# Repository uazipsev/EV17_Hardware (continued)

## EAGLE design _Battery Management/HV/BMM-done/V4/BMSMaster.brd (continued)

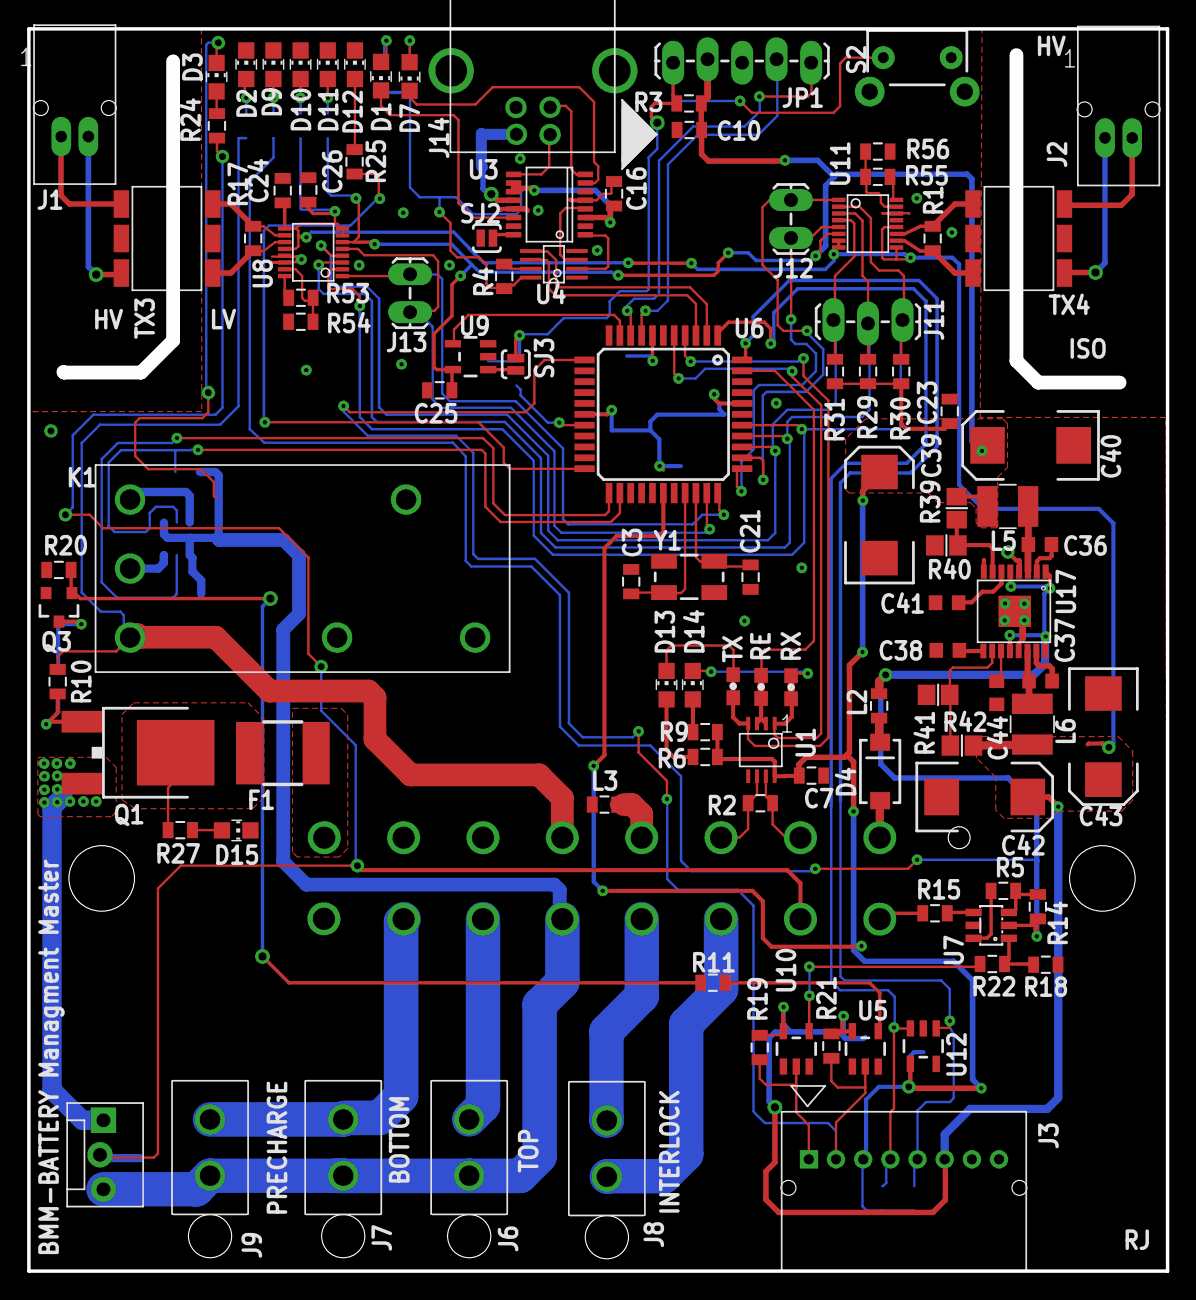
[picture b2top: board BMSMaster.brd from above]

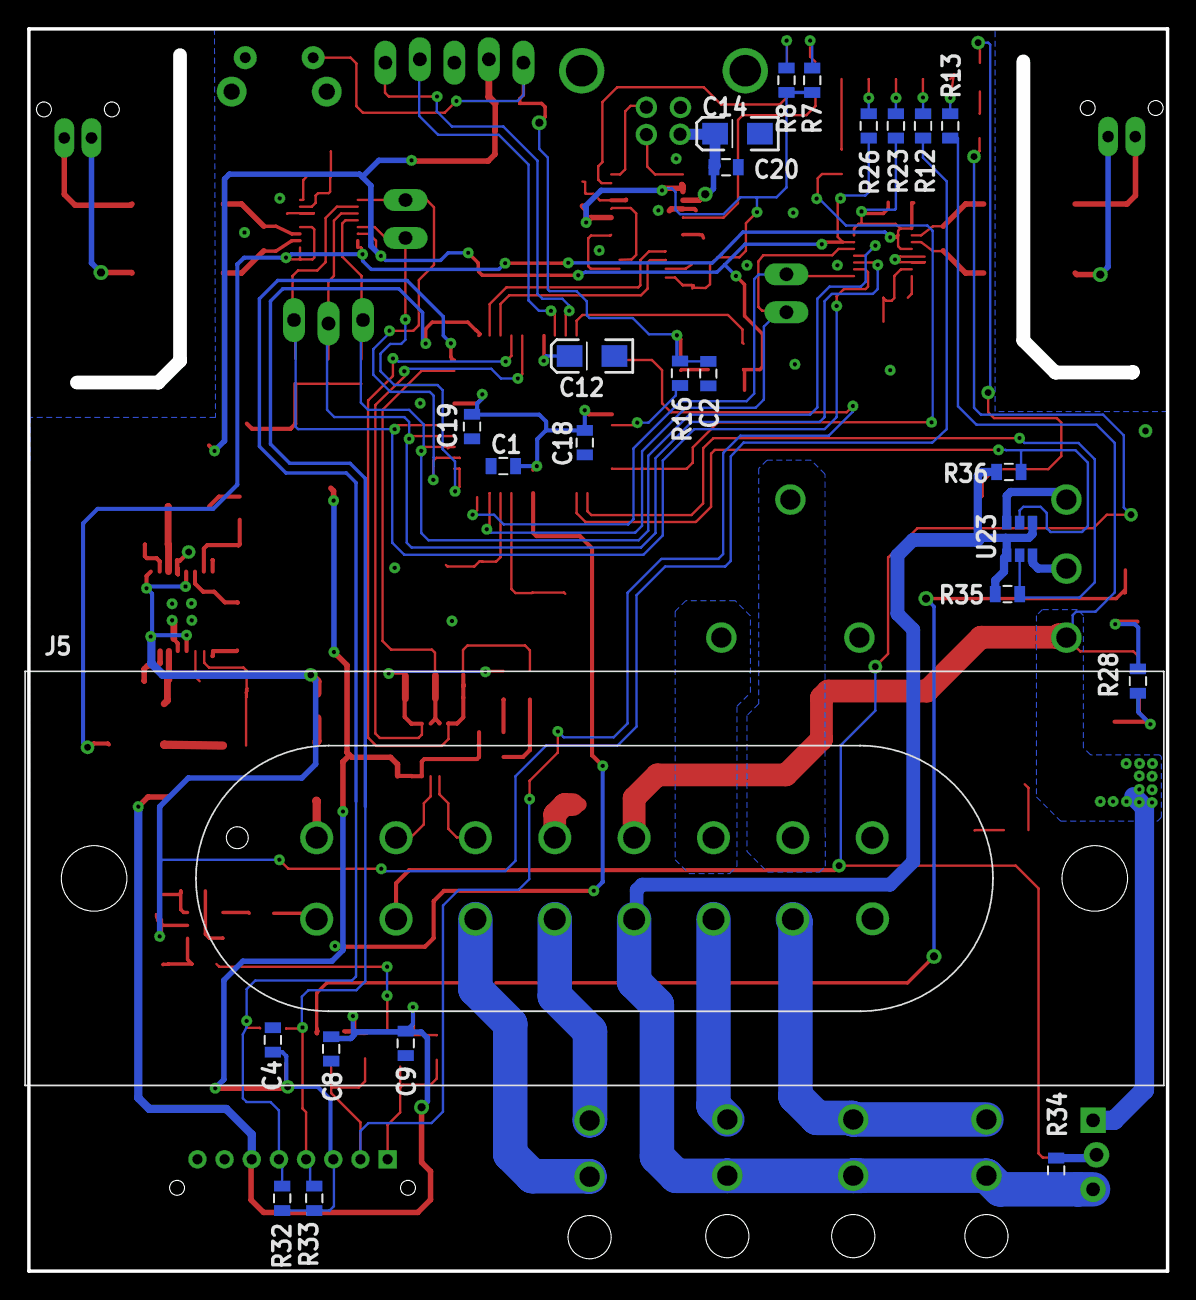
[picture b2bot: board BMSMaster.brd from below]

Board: 2 copper layers, 83.8 x 91.4 mm, 129 parts (25 on the bottom side), 100 nets.

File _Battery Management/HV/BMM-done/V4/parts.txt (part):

Partlist

Exported from BMSMaster.sch at 4/28/2016 8:13 PM

EAGLE Version 7.5.0 Copyright (c) 1988-2015 CadSoft

Assembly variant: 

Part     Value             Device                  Package                  Library                    Sheet

C1       0.1UF             CAP_0.1UF_50V_0805      0805                     FSAE Electric              1
C2       0.1UF             CAP_0.1UF_50V_0805      0805                     FSAE Electric              1
C3       12PF              CAP_12PF_50V_0805       0805                     FSAE Electric              1
C4       0.1UF             CAP_0.1UF_50V_0805      0805                     FSAE Electric              1
C5       10UF              CAP-POL_10UF_16V        EIA3216-16V              FSAE Electric              1
C6       10UF              CAP-POL_10UF_16V        EIA3216-16V              FSAE Electric              1
C7       0.1UF             CAP_0.1UF_50V_0805      0805                     FSAE Electric              1
C8       0.1UF             CAP_0.1UF_50V_0805      0805                     FSAE Electric              1
C9       0.1UF             CAP_0.1UF_50V_0805      0805                     FSAE Electric              1
C12      10UF              CAP-POL_10UF_16V        EIA3216-16V              FSAE Electric              1
C14      10UF              CAP-POL_10UF_16V        EIA3216-16V              FSAE Electric              1
C16      0.1UF             CAP_0.1UF_50V_0805      0805                     FSAE Electric              1
C18      0.1UF             CAP_0.1UF_50V_0805      0805                     FSAE Electric              1
C19      0.1UF             CAP_0.1UF_50V_0805      0805                     FSAE Electric              1
C20      0.1UF             CAP_0.1UF_50V_0805      0805                     FSAE Electric              1
C21      12PF              CAP_12PF_50V_0805       0805                     FSAE Electric              1
C23      0.1UF             CAP_0.1UF_50V_0805      0805                     FSAE Electric              1
C24      0.1UF             CAP_0.1UF_50V_0805      0805                     FSAE Electric              1
C25      0.1UF             CAP_0.1UF_50V_0805      0805                     FSAE Electric              1
C26      0.1UF             CAP_0.1UF_50V_0805      0805                     FSAE Electric              1
C27      10UF              CAP-POL_10UF_16V        EIA3216-16V              FSAE Electric              1
C28      10UF              CAP-POL_10UF_16V        EIA3216-16V              FSAE Electric              1
D1       GREEN             LED_GREEN               CHIP_LED0805             FSAE Electric              1
D2       GREEN             LED_GREEN               CHIP_LED0805             FSAE Electric              1
D3       ORANGE            LED_ORANGE              CHIP_LED0805             FSAE Electric              1
D4       RF201L2STE25      DIODE_RF201L2STE25      SMA                      FSAE Electric              1
D7       GREEN             LED_GREEN               CHIP_LED0805             FSAE Electric              1
D9       GREEN             LED_GREEN               CHIP_LED0805             FSAE Electric              1
D10      GREEN             LED_GREEN               CHIP_LED0805             FSAE Electric              1
D11      GREEN             LED_GREEN               CHIP_LED0805             FSAE Electric              1
D12      AMBER             LED_AMBER               CHIP_LED0805             FSAE Electric              1
D13      GREEN             LED_GREEN               CHIP_LED0805             FSAE Electric              1
D14      RED               LED_RED                 CHIP_LED0805             FSAE Electric              1
D15      GREEN             LED_GREEN               CHIP_LED0805             FSAE Electric              1
f       550MA             PTC_550MA_60V           2018                     FSAE Electric              1
J1       M2_DF13-2P        M2_DF13-2P              DF13-2P                  FSAE Electric              1
J2       M2_DF13-2P        M2_DF13-2P              DF13-2P                  FSAE Electric              1
J3       M4_1X4_LOCK       M4_1X4_LOCK             MOLEX_1X4                FSAE Electric              1
J4       M80022232081-2    M80022232081-2          MOLEX-1X8-2              FSAE Electric              1
J5       M16_M_194280016   M16_M_194280016         19428-0016               FSAE Electric              1
J6       M2770166          M2770166                1-770166-0               FSAE Electric              1
J7       M2770166          M2770166                1-770166-0               FSAE Electric              1
J8       M2770166          M2770166                1-770166-0               FSAE Electric              1
J9       M2770166          M2770166                1-770166-0               FSAE Electric              1
J10      IMD               M3M1X3                  MOLEX-1X3                FSAE Electric              1
JP1                        M05LOCK_LONGPADS        1X05_LOCK_LONGPADS       SparkFun-Connectors        1
K1       ADJ14024          ADJ14024                ADJ14024                 FSAE Electric              1
L2       L_FB_2A           L_FB_2A                 0805                     FSAE Electric              1
L3       L_FB_2A           L_FB_2A                 0805                     FSAE Electric              1
L5       L_FB_2A           L_FB_2A                 0805                     FSAE Electric              1
Q1       IRFR9120TRPBF     MOS-P_IRFR9120TRPBF     DPAK                     FSAE Electric              1
Q3       BSS123            MOS-N_BSS123            SOT23                    FSAE Electric              1
R1       120               RES_120_1%_0805         0805                     FSAE Electric              1
R2       120               RES_120_1%_0805         0805                     FSAE Electric              1
R3       10K               RES_10K_1%_0805         0805                     FSAE Electric              1
R4       1K                RES_1K_1%_0805          0805                     FSAE Electric              1
R5       1K                RES_1K_1%_0805          0805                     FSAE Electric              1
R6       1k                RES_1K_1%_0805          0805                     FSAE Electric              1
R7       1K                RES_1K_1%_0805          0805                     FSAE Electric              1
R8       1K                RES_1K_1%_0805          0805                     FSAE Electric              1
R9       1k                RES_1K_1%_0805          0805                     FSAE Electric              1
R10      22K               RES_22K_1%_0805         0805                     FSAE Electric              1
R11      1K                RES_1K_1%_0805          0805                     FSAE Electric              1
R12      1.2K              RES_1.2K_1%_0805        0805                     FSAE Electric              1
R13      3.3K              RES_3.3K_1%_0805        0805                     FSAE Electric              1
R14      10K               RES_10K_1%_0805         0805                     FSAE Electric              1
R15      10K               RES_10K_1%_0805         0805                     FSAE Electric              1
R16      499               RES_499_1%_0805         0805                     FSAE Electric              1
R17      120               RES_120_1%_0805         0805                     FSAE Electric              1
R18      100K              RES_100K_1%_0805        0805                     FSAE Electric              1
R19      2.2K              RES_2.2K_1%_0805        0805                     FSAE Electric              1
R20      100K              RES_100K_1%_0805        0805                     FSAE Electric              1
R21      2.2K              RES_2.2K_1%_0805        0805                     FSAE Electric              1
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
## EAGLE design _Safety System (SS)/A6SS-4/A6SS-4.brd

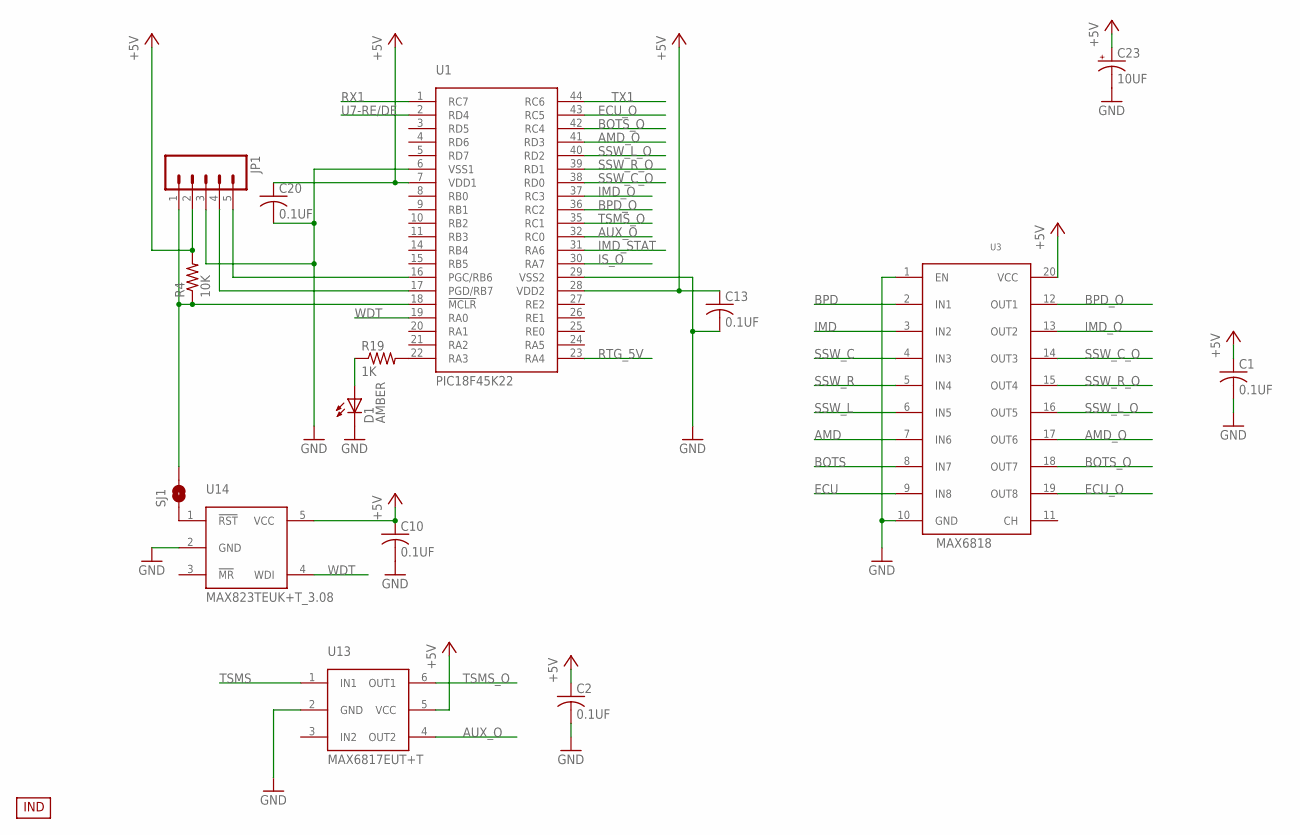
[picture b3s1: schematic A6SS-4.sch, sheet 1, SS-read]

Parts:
C1, C2, C10, C13, C20: 0.1UF; 0805
C23: 10UF; EIA3216-16V
D1: AMBER; CHIP_LED0805
JP1: M05LOCK_LONGPADS; 1X05_LOCK_LONGPADS
R4: 10K; 0805
R19: 1K; 0805
SJ1: SOLDERJUMPERNO; SJ_2S-NO
U1: PIC18F45K22; TQFP-44
U3: MAX6818; SSOP-20
U13: MAX6817EUT+T; SOT23-6
U14: MAX823TEUK+T_3.08; SOT23-5
U$1: INDPK1; PICKIT-PIN-1

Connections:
+5V: C1.1 (+), C2.1 (+), C10.1 (+), C13.1 (+), C20.1 (+), C23.A (+), JP1.2, R4.2, U1.7 (VDD1), U1.28 (VDD2), U3.20 (VCC), U13.5 (VCC), U14.5 (VCC); also elsewhere on the board
AMD: U3.7 (IN6); also elsewhere on the board
AMD_O: U1.41 (RD3), U3.17 (OUT6)
AUX_O: U1.32 (RC0), U13.4 (OUT2)
BOTS: U3.8 (IN7); also elsewhere on the board
BOTS_O: U1.42 (RC4), U3.18 (OUT7)
BPD: U3.2 (IN1); also elsewhere on the board
BPD_O: U1.36 (RC2), U3.12 (OUT1)
ECU: U3.9 (IN8); also elsewhere on the board
ECU_O: U1.43 (RC5), U3.19 (OUT8)
GND: C1.2 (-), C2.2 (-), C10.2 (-), C13.2 (-), C20.2 (-), C23.C (-), D1.C, JP1.3, U1.6 (VSS1), U1.29 (VSS2), U3.1 (EN), U3.10 (GND), U13.2 (GND), U14.2 (GND); also elsewhere on the board
IMD: U3.3 (IN2); also elsewhere on the board
IMD_O: U1.37 (RC3), U3.13 (OUT2)
IMD_STAT: U1.31 (RA6); also elsewhere on the board
IS_O: U1.30 (RA7); also elsewhere on the board
unnamed: SJ1.1, U14.1 (!RST)
unnamed: D1.A, R19.1
unnamed: R19.2, U1.22 (RA3)
unnamed: JP1.4, U1.17 (PGD/RB7)
unnamed: JP1.5, U1.16 (PGC/RB6)
unnamed: JP1.1, R4.1, SJ1.2, U1.18 (!MCLR)
RTG_5V: U1.23 (RA4); also elsewhere on the board
RX1: U1.1 (RC7); also elsewhere on the board
SSW_C: U3.4 (IN3); also elsewhere on the board
SSW_C_O: U1.38 (RD0), U3.14 (OUT3)
SSW_L: U3.6 (IN5); also elsewhere on the board
SSW_L_O: U1.40 (RD2), U3.16 (OUT5)
SSW_R: U3.5 (IN4); also elsewhere on the board
SSW_R_O: U1.39 (RD1), U3.15 (OUT4)
TSMS: U13.1 (IN1); also elsewhere on the board
TSMS_O: U1.35 (RC1), U13.6 (OUT1)
TX1: U1.44 (RC6); also elsewhere on the board
U7-RE/DE: U1.2 (RD4); also elsewhere on the board
WDT: U1.19 (RA0), U14.4 (WDI)

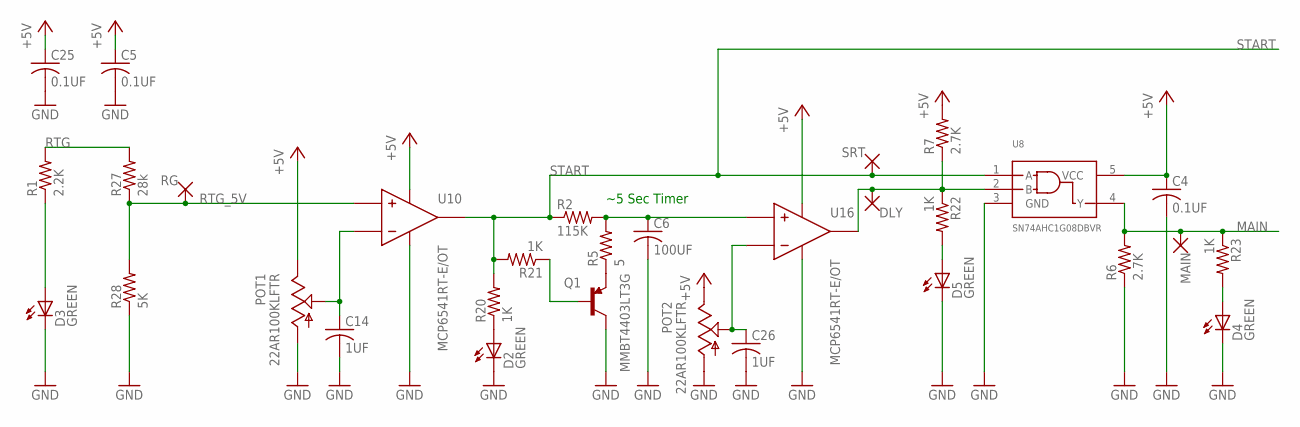
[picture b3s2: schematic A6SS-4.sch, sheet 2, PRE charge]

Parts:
C4, C5, C25: 0.1UF; 0805
C6: 100UF; 1206
C14, C26: 1UF; 0805
D2, D3, D4, D5: GREEN; CHIP_LED0805
DLY: TP; 0603
MAIN: TP; 0603
POT1, POT2: 22AR100KLFTR
Q1: MMBT4403LT3G; SOT23
R1: 2.2K; 0805
R2: 115K; 0805
R5: 5; 0805
R6, R7: 2.7K; 0805
R20, R21, R22, R23: 1K; 0805
R27: 28k; 0805
R28: 5K; 0805
RG: TP; 0603
SRT: TP; 0603
U8: SN74AHC1G08DBVR; SOT23-5
U10, U16: MCP6541RT-E/OT; SOT23-5

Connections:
+5V: C4.1 (+), C5.1 (+), C25.1 (+), POT1.1 (CCW), POT2.1 (CCW), R7.2, U8.5 (VCC), U10.2 (VDD), U16.2 (VDD); also elsewhere on the board
GND: C4.2 (-), C5.2 (-), C6.2 (-), C14.2 (-), C25.2 (-), C26.2 (-), D2.C, D3.C, D4.C, D5.C, POT1.3 (CW), POT2.3 (CW), Q1.3 (C), R6.1, R28.1, U8.3 (GND), U10.5 (GND), U16.5 (GND); also elsewhere on the board
MAIN: MAIN.1, MAIN.2, R6.2, R23.1, U8.4 (Y); also elsewhere on the board
unnamed: C26.1 (+), POT2.2 (W), U16.4 (-)
unnamed: Q1.1 (B), R21.1
unnamed: Q1.2 (E), R5.1
unnamed: C14.1 (+), POT1.2 (W), U10.4 (-)
unnamed: D2.A, R20.1
unnamed: D3.A, R1.1
unnamed: C6.1 (+), R2.2, R5.2, U16.3 (+)
unnamed: DLY.1, DLY.2, R7.1, R22.1, U8.2 (B), U16.1 (VOUT)
unnamed: D4.A, R23.2
unnamed: D5.A, R22.2
RTG: R1.2, R27.2; also elsewhere on the board
RTG_5V: R27.1, R28.2, RG.1, RG.2, U10.3 (+); also elsewhere on the board
START: R2.1, R20.2, R21.2, SRT.1, SRT.2, U8.1 (A), U10.1 (VOUT); also elsewhere on the board

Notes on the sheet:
~5 Sec Timer

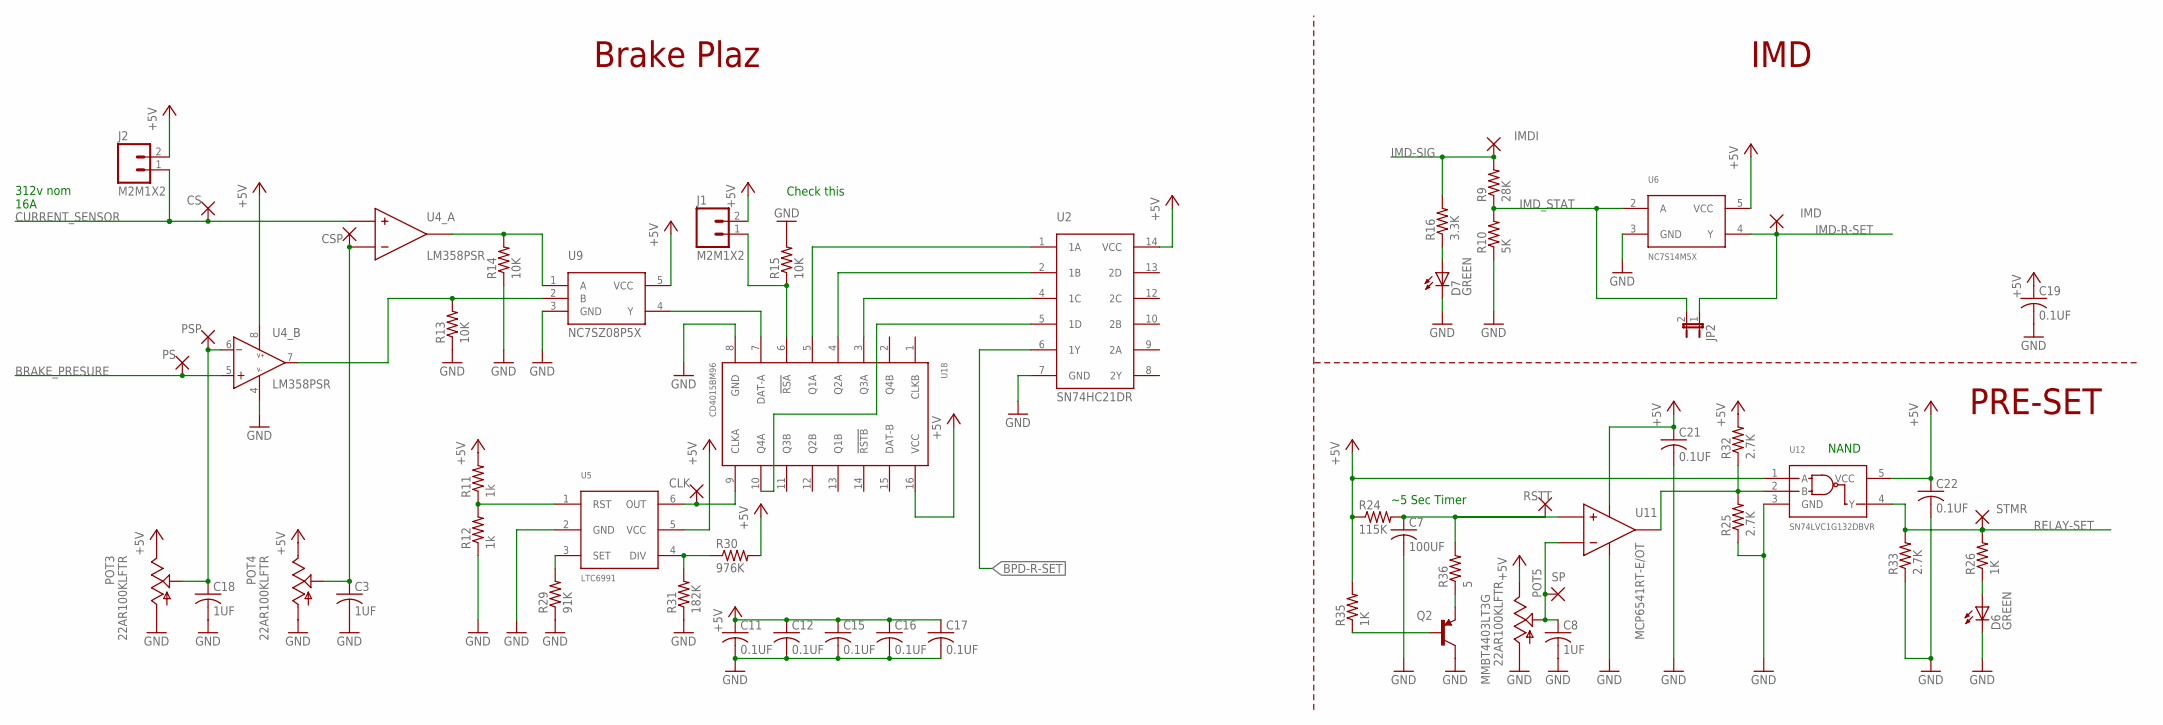
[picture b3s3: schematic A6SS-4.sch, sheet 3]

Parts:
C3, C8, C18: 1UF; 0805
C7: 100UF; 1206
C11, C12, C15, C16, C17, C19, C21, C22: 0.1UF; 0805
CLK: TP; 0603
CS: TP; 0603
CSP: TP; 0603
D6, D7: GREEN; CHIP_LED0805
IMD: TP; 0603
IMDI: TP; 0603
J1, J2: M2M1X2; MOLEX-1X2
JP2: JUMPER-2SMD-NO; SJ_2S-NO
POT3, POT4, POT5: 22AR100KLFTR
PS: TP; 0603
PSP: TP; 0603
Q2: MMBT4403LT3G; SOT23
R9: 28K; 0805
R10: 5K; 0805
R11, R12: 1k; 0805
R13, R14, R15: 10K; 0805
R16: 3.3K; 0805
R24: 115K; 0805
R25, R32, R33: 2.7K; 0805
R26, R35: 1K; 0805
R29: 91K; 0805
R30: 976K; 0805
R31: 182K; 0805
R36: 5; 0805
RSTT: TP; 0603
SP: TP; 0603
STMR: TP; 0603
U2: SN74HC21DR; SO-14
U4: LM358PSR; SO-8
U5: LTC6991; TSOT-23-6
U6: NC7S14M5X; SOT23-5
U9: NC7SZ08P5X; SC-70-5
U11: MCP6541RT-E/OT; SOT23-5
U12: SN74LVC1G132DBVR; SOT23-5
U18: CD4015BM96; SO-16

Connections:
+5V: C11.1 (+), C12.1 (+), C15.1 (+), C16.1 (+), C17.1 (+), C19.1 (+), C21.1 (+), C22.1 (+), J1.2, J2.2, POT3.1 (CCW), POT4.1 (CCW), POT5.1 (CCW), R11.2, R24.1, R30.2, R32.2, R35.2, U2.14 (VCC), U4.8 (V+), U5.5 (VCC), U6.5 (VCC), U9.5 (VCC), U11.2 (VDD), U12.1 (A), U12.5 (VCC), U18.16 (VCC); also elsewhere on the board
BPD-R-SET: U2.6 (1Y); also elsewhere on the board
BRAKE_PRESURE: PS.1, PS.2, U4.5 (+); also elsewhere on the board
CURRENT_SENSOR: CS.1, CS.2, J2.1, U4.3 (+); also elsewhere on the board
GND: C3.2 (-), C7.2 (-), C8.2 (-), C11.2 (-), C12.2 (-), C15.2 (-), C16.2 (-), C17.2 (-), C18.2 (-), C19.2 (-), C21.2 (-), C22.2 (-), D6.C, D7.C, POT3.3 (CW), POT4.3 (CW), POT5.3 (CW), Q2.3 (C), R10.1, R12.1, R13.1, R14.1, R15.2, R25.1, R29.1, R31.1, R33.1, U2.7 (GND), U4.4 (V-), U5.2 (GND), U6.3 (GND), U9.3 (GND), U11.5 (GND), U12.3 (GND), U18.8 (GND); also elsewhere on the board
IMD-R-SET: IMD.1, IMD.2, JP2.1, U6.4 (Y); also elsewhere on the board
IMD-SIG: IMDI.1, IMDI.2, R9.2, R16.2; also elsewhere on the board
IMD_STAT: JP2.2, R9.1, R10.2, U6.2 (A); also elsewhere on the board
unnamed: C8.1 (+), POT5.2 (W), SP.1, SP.2, U11.4 (-)
unnamed: U2.5 (1D), U18.10 (Q4A)
unnamed: R30.1, R31.2, U5.4 (DIV)
unnamed: D7.A, R16.1
unnamed: U9.4 (Y), U18.7 (DAT-A)
unnamed: J1.1, R15.1, U18.6 (!RSA)
unnamed: U2.1 (1A), U18.5 (Q1A)
unnamed: U2.2 (1B), U18.4 (Q2A)
unnamed: U2.4 (1C), U18.3 (Q3A)
unnamed: R29.2, U5.3 (SET)
unnamed: CLK.1, CLK.2, U5.6 (OUT), U18.9 (CLKA)
unnamed: C3.1 (+), CSP.1, CSP.2, POT4.2 (W), U4.2 (-)
unnamed: R25.2, R32.1, U11.1 (VOUT), U12.2 (B)
unnamed: R11.1, R12.2, U5.1 (RST)
unnamed: C18.1 (+), POT3.2 (W), PSP.1, PSP.2, U4.6 (-)
unnamed: R14.2, U4.1 (VOUT), U9.1 (A)
unnamed: D6.A, R26.1
unnamed: R13.2, U4.7 (O), U9.2 (B)
unnamed: Q2.1 (B), R35.1
unnamed: Q2.2 (E), R36.1
unnamed: C7.1 (+), R24.2, R36.2, RSTT.1, RSTT.2, U11.3 (+)
RELAY-SET: R26.2, R33.2, STMR.1, STMR.2, U12.4 (Y); also elsewhere on the board

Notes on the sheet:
312v nom 16A
Check this
Brake Plaz
IMD
PRE-SET
~5 Sec Timer
NAND

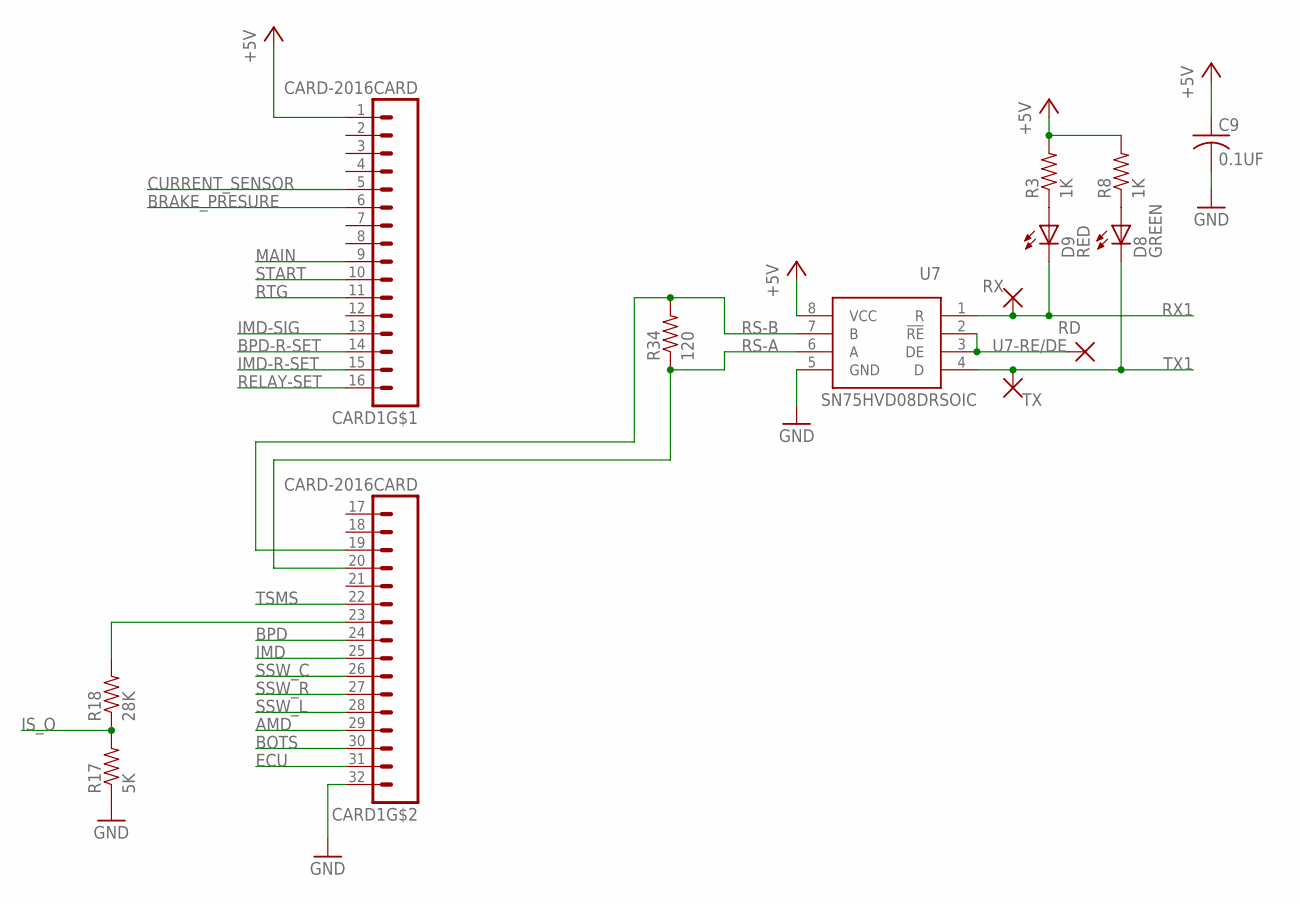
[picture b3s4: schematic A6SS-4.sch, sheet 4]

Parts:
C9: 0.1UF; 0805
CARD1: CARD-2016CARD; CARD-2016
D8: GREEN; CHIP_LED0805
D9: RED; CHIP_LED0805
R3, R8: 1K; 0805
R17: 5K; 0805
R18: 28K; 0805
R34: 120; 0805
RD: TP; 0603
RX: TP; 0603
TX: TP; 0603
U7: SN75HVD08DRSOIC; SO-8

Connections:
+5V: C9.1 (+), CARD1.1, R3.2, R8.2, U7.8 (VCC); also elsewhere on the board
AMD: CARD1.29 (13); also elsewhere on the board
BOTS: CARD1.30 (14); also elsewhere on the board
BPD: CARD1.24 (8); also elsewhere on the board
BPD-R-SET: CARD1.14; also elsewhere on the board
BRAKE_PRESURE: CARD1.6; also elsewhere on the board
CURRENT_SENSOR: CARD1.5; also elsewhere on the board
ECU: CARD1.31 (15); also elsewhere on the board
GND: C9.2 (-), CARD1.32 (16), R17.1, U7.5 (GND); also elsewhere on the board
IMD: CARD1.25 (9); also elsewhere on the board
IMD-R-SET: CARD1.15; also elsewhere on the board
IMD-SIG: CARD1.13; also elsewhere on the board
IS_O: R17.2, R18.1; also elsewhere on the board
MAIN: CARD1.9; also elsewhere on the board
unnamed: CARD1.23 (7), R18.2
unnamed: D9.A, R3.1
unnamed: D8.A, R8.1
RELAY-SET: CARD1.16; also elsewhere on the board
RS-A: CARD1.20 (4), R34.1, U7.6 (A)
RS-B: CARD1.19 (3), R34.2, U7.7 (B)
RTG: CARD1.11; also elsewhere on the board
RX1: D9.C, RX.1, RX.2, U7.1 (R); also elsewhere on the board
SSW_C: CARD1.26 (10); also elsewhere on the board
SSW_L: CARD1.28 (12); also elsewhere on the board
SSW_R: CARD1.27 (11); also elsewhere on the board
START: CARD1.10; also elsewhere on the board
TSMS: CARD1.22 (6); also elsewhere on the board
TX1: D8.C, TX.1, TX.2, U7.4 (D); also elsewhere on the board
U7-RE/DE: RD.1, RD.2, U7.2 (!RE), U7.3 (DE); also elsewhere on the board
